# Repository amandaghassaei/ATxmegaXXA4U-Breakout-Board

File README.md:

# ATxmegaXXA4U-Breakout-Board
Eagle Schematics and Design for a DIY milled XMEGA breakout board.  Pin compatible with ATxmega16A4U, ATxmega64A4U, and ATxmeg32A4U, ATxmega128A4U.

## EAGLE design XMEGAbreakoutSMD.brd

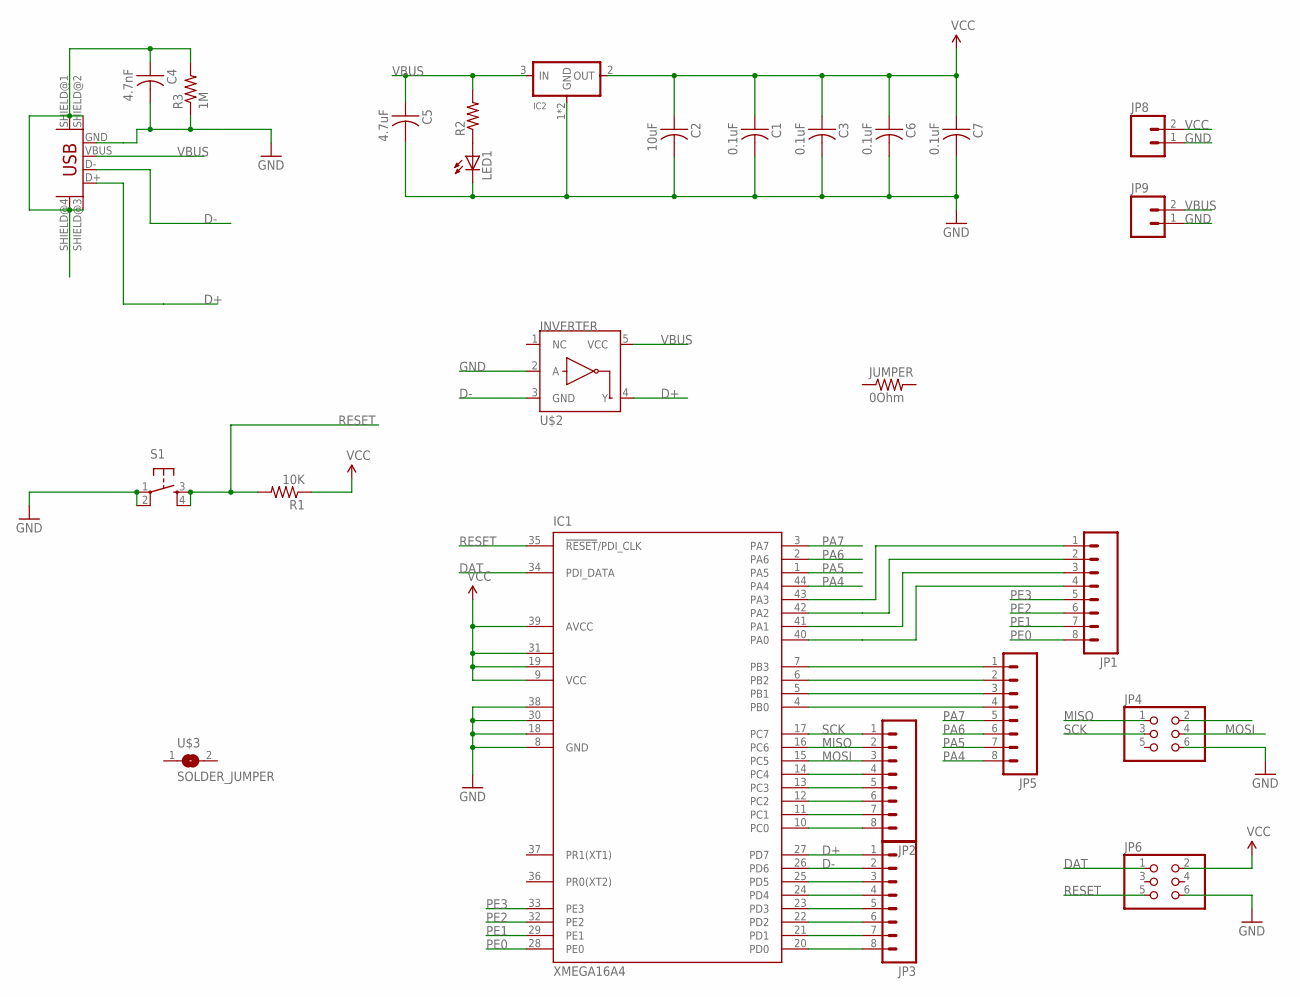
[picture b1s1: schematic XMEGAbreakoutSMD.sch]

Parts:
C1, C6, C7: 0.1uF; C1206
C2: 10uF; C1206
C3: 0.1uF; C1206FAB
C4: 4.7nF; C1206
C5: 4.7uF; C1206
IC1: XMEGA16A4; TQFP44-FAB
IC2: REGULATORSOT223; SOT223
JP1: M08; 1X08_SMD_ALT_2X1X4
JP2, JP3, JP5: M08SMD-STRAIGHT-ALT; 1X08_SMD_ALT
JP4, JP6: PINHD-2X3-SMD; 2X03SMD
JP8, JP9: M02; 1X02_SMD_STRAIGHT_ALT
JUMPER: 0Ohm; R1206FAB
LED1: LEDSMT1206; 1206
R1: 10K; R1206FAB
R2: RES-US1206FAB; R1206FAB
R3: 1M; R1206FAB
S1: 6MM_SWITCH6MM_SWITCH; 6MM_SWITCH
U$1: USB_MINIB
U$2: INVERTER; SOT23-5
U$3: SOLDER_JUMPER; SJFAB

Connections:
D+: IC1.27 (PD7), JP3.1, U$1.D+, U$2.4 (Y)
D-: IC1.26 (PD6), JP3.2, U$1.D-, U$2.3 (GND)
DAT: IC1.34 (PDI_DATA), JP6.1
GND: C1.2, C2.2, C3.2, C4.2, C5.2, C6.2, C7.2, IC1.8 (GND), IC1.18 (GND1), IC1.30 (GND2), IC1.38 (GND3), IC2.1 (GND), IC2.4 (GND), JP4.6, JP6.6, JP8.1, JP9.1, LED1.C, R3.1, S1.1, S1.2 (P1), U$1.GND, U$2.2 (A)
MISO: IC1.16 (PC6), JP2.2, JP4.1
MOSI: IC1.15 (PC5), JP2.3, JP4.4
unnamed: IC1.43 (PA3), JP1.1
unnamed: IC1.42 (PA2), JP1.2
unnamed: IC1.41 (PA1), JP1.3
unnamed: IC1.40 (PA0), JP1.4
unnamed: IC1.7 (PB3), JP5.1
unnamed: IC1.6 (PB2), JP5.2
unnamed: IC1.5 (PB1), JP5.3
unnamed: IC1.14 (PC4), JP2.4
unnamed: IC1.13 (PC3), JP2.5
unnamed: IC1.12 (PC2), JP2.6
unnamed: IC1.11 (PC1), JP2.7
unnamed: IC1.10 (PC0), JP2.8
unnamed: IC1.4 (PB0), JP5.4
unnamed: IC1.25 (PD5), JP3.3
unnamed: IC1.24 (PD4), JP3.4
unnamed: IC1.23 (PD3), JP3.5
unnamed: IC1.22 (PD2), JP3.6
unnamed: IC1.21 (PD1), JP3.7
unnamed: IC1.20 (PD0), JP3.8
unnamed: C4.1, R3.2, U$1.SHIELD@1 (SHIELD), U$1.SHIELD@2 (SHIELD1), U$1.SHIELD@3 (SHIELD2), U$1.SHIELD@4 (SHIELD3)
unnamed: LED1.A, R2.1
PA4: IC1.44 (PA4), JP5.8
PA5: IC1.1 (PA5), JP5.7
PA6: IC1.2 (PA6), JP5.6
PA7: IC1.3 (PA7), JP5.5
PE0: IC1.28 (PE0), JP1.8
PE1: IC1.29 (PE1), JP1.7
PE2: IC1.32 (PE2), JP1.6
PE3: IC1.33 (PE3), JP1.5
RESET: IC1.35 (!RESET!/PDI_CLK), JP6.5, R1.2, S1.3 (S), S1.4 (S1)
SCK: IC1.17 (PC7), JP2.1, JP4.3
VBUS: C5.1, IC2.3 (IN), JP9.2, R2.2, U$1.VBUS, U$2.5 (VCC)
VCC: C1.1, C2.1, C3.1, C6.1, C7.1, IC1.9 (VCC), IC1.19 (VCC1), IC1.31 (VCC2), IC1.39 (AVCC), IC2.2 (OUT), JP6.2, JP8.2, R1.1

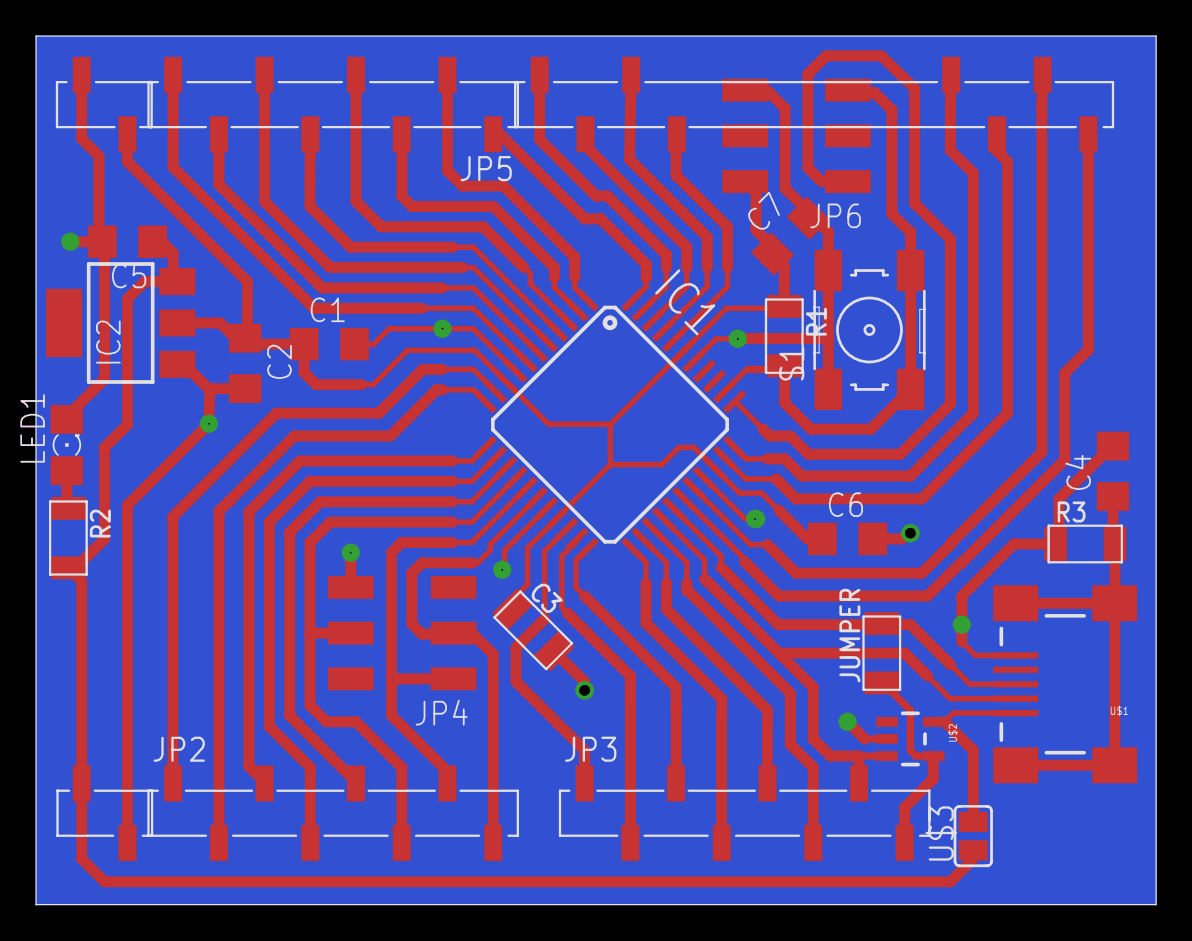
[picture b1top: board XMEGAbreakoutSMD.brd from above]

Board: 2 copper layers, 62.2 x 48.3 mm, 26 parts (0 on the bottom side), 39 nets.

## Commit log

2016-01-06 typo
2016-01-06 smd breakout finished
2016-01-06 eagle layout finished
2016-01-06 final output pngs
2016-01-06 final designs
2016-01-06 small changes
2016-01-07 diode array
2016-01-07 final
2016-01-07 png changes
2016-01-07 reorganizing
2016-01-07 added power pins
2016-01-08 power pins broken out
2016-01-12 latest
2016-01-13 flipped bottom layer
2016-05-23 fix to smd board
2016-05-24 d+ and d- switched
2016-05-25 final pngs
2016-05-25 small fix
2016-05-26 flipped bottom png
2016-05-26 added border
2016-05-28 change th dim
2016-05-28 solder jumper on 5V
2016-05-29 fixes to boundaries
2016-05-29 flip back
2016-05-29 organization
2016-05-29 widen holes
2016-06-28 caps on each port
2016-06-28 600dpi
2016-06-28 smal changes
2016-06-28 thermals

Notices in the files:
parts and their libraries:
SparkFun: Licensing: CC v3.0 Share-Alike You are welcome to use this library for commercial purposes.
